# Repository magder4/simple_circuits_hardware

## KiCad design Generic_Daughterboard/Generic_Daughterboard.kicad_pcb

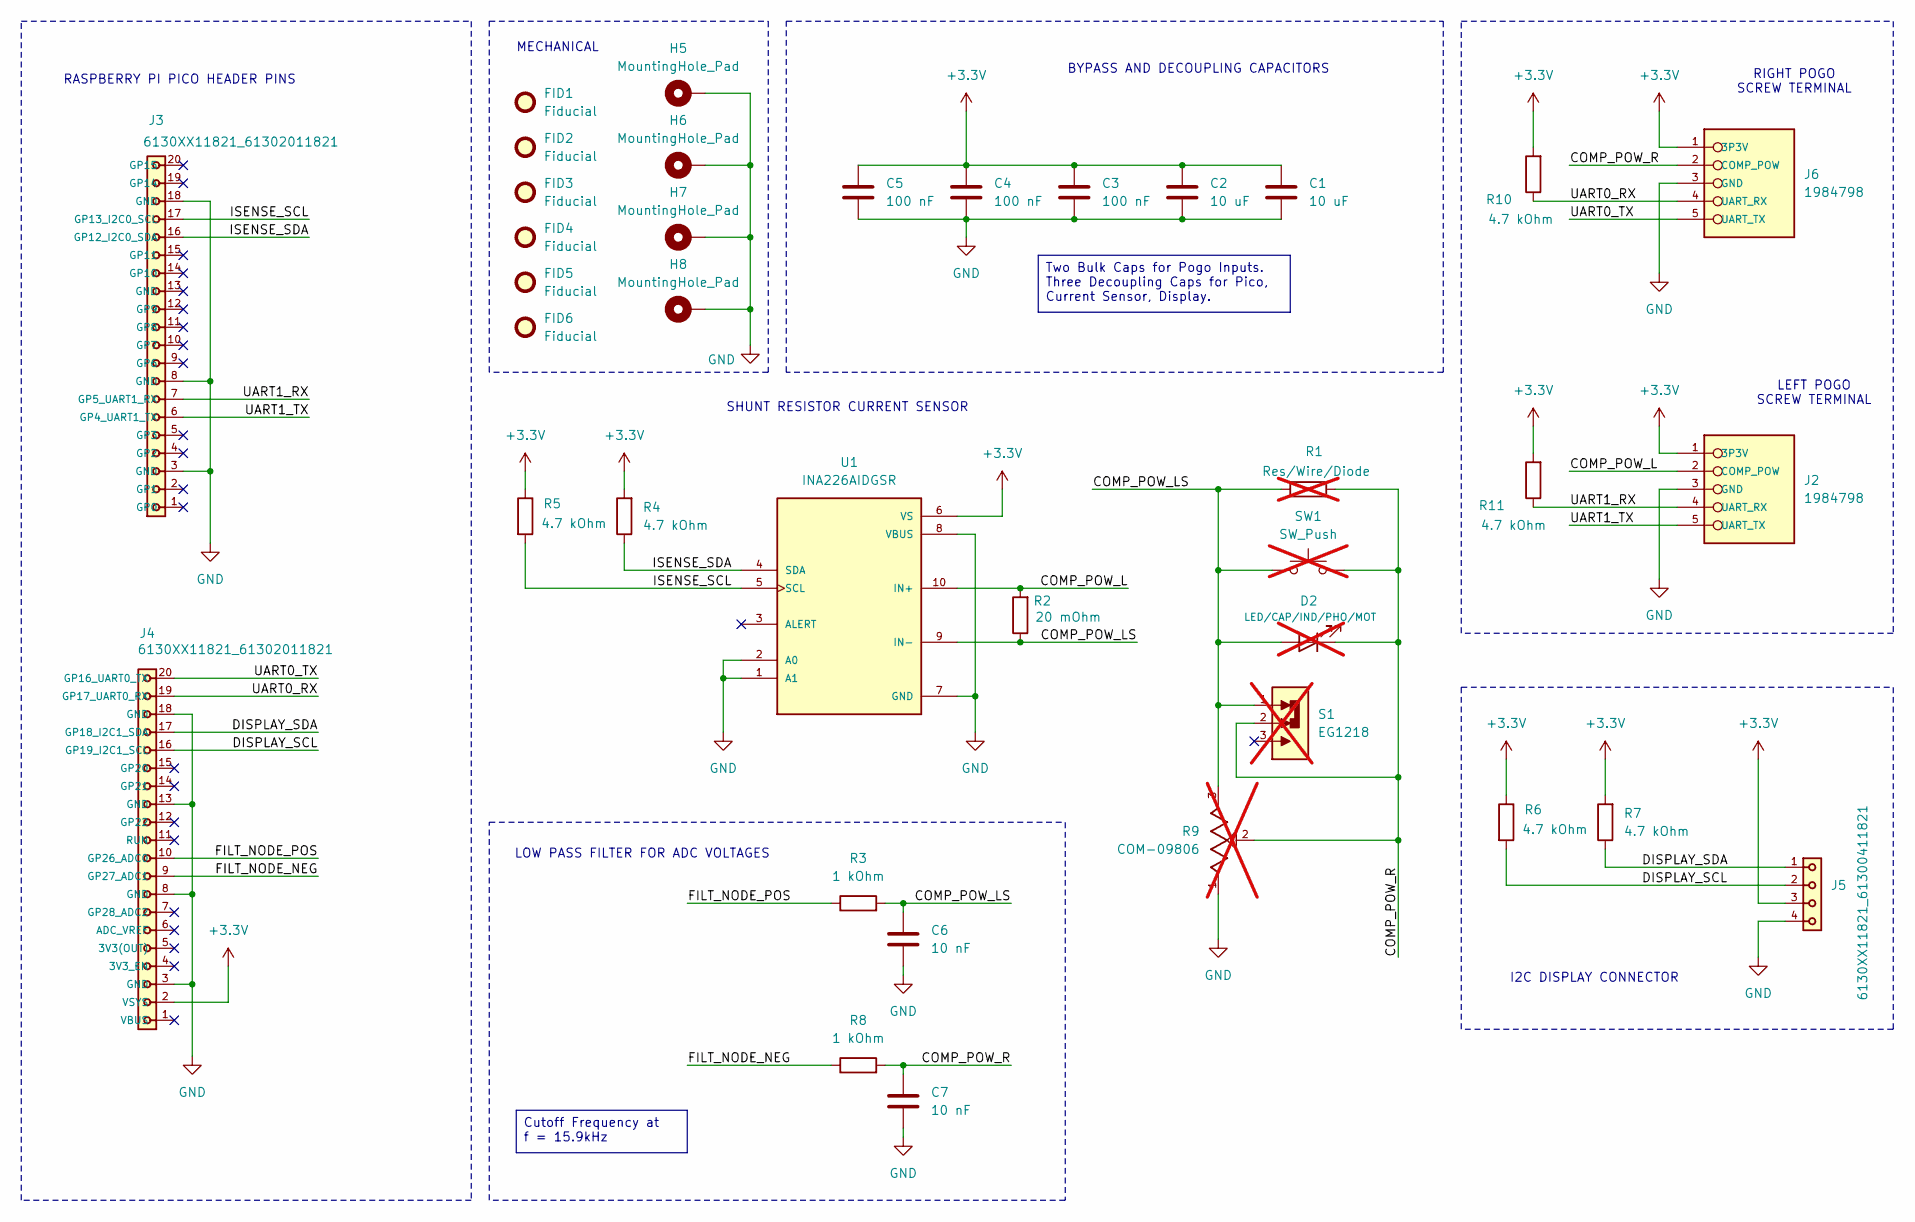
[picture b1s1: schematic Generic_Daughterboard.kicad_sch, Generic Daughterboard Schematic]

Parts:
C1, C2: 10 uF; C_0402_1005Metric
C3, C4, C5: 100 nF; C_0402_1005Metric
C6, C7: 10 nF; C_0402_1005Metric
D2: LED/CAP/IND/PHO/MOT; LED_D5.0mm_Clear; not fitted
FID1, FID2, FID3, FID4, FID5, FID6: Fiducial; Fiducial_0.5mm_Mask1.5mm
H5, H6, H7, H8: MountingHole_Pad; MountingHole_2.2mm_M2_Pad
J2, J6: 1984798; PHOENIX_1984798; MPN 1984798
J3, J4: 6130XX11821_61302011821; 61302011821; DigiKey_Part_Number 732-61302011821-ND
J5: 6130XX11821_61300411821; 61300411821; DigiKey_Part_Number 732-61300411821-ND
R1: Res/Wire/Diode; R_Axial_DIN0207_L6.3mm_D2.5mm_P10.16mm_Horizontal; not fitted
R2: 20 mOhm; R_0805_2012Metric
R3, R8: 1 kOhm; R_0402_1005Metric
R4, R5, R6, R7, R10, R11: 4.7 kOhm; R_0603_1608Metric
R9: COM-09806; TRIM_COM-09806; MPN COM-09806; not fitted
S1: EG1218; SW_EG1218; MPN EG1218; not fitted
SW1: SW_Push; SW_TH_Tactile_Omron_B3F-102x; not fitted
U1: INA226AIDGSR; SOP50P490X110-10N; PARTREV B; DigiKey_Part_Number 296-29034-1-ND

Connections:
+3.3V: C1.1, C2.2, C3.2, C4.2, C5.2, J2.1 (3P3V), J4.2 (VSYS), J5.3, J6.1 (3P3V), R4.2, R5.1, R6.1, R7.2, R10.2, R11.2, U1.6 (VS)
/COMP_POW_L: J2.2 (COMP_POW), R2.2, U1.10 (IN+)
/COMP_POW_LS: C6.2, D2.2 (A), R1.2, R2.1, R3.2, R9.3, S1.1, SW1.1, U1.9 (IN-)
/COMP_POW_R: C7.2, D2.1 (K), J6.2 (COMP_POW), R1.1, R8.2, R9.2, S1.2, SW1.2
/DISPLAY_SCL: J4.16 (GP19_I2C1_SCL), J5.2, R6.2
/DISPLAY_SDA: J4.17 (GP18_I2C1_SDA), J5.1, R7.1
/FILT_NODE_NEG: J4.9 (GP27_ADC1), R8.1
/FILT_NODE_POS: J4.10 (GP26_ADC0), R3.1
/ISENSE_SCL: J3.17 (GP13_I2C0_SCL), R5.2, U1.5 (SCL)
/ISENSE_SDA: J3.16 (GP12_I2C0_SDA), R4.1, U1.4 (SDA)
/UART0_RX: J4.19 (GP17_UART0_RX), J6.4 (UART_RX), R10.1
/UART0_TX: J4.20 (GP16_UART0_TX), J6.5 (UART_TX)
/UART1_RX: J2.4 (UART_RX), J3.7 (GP5_UART1_RX), R11.1
/UART1_TX: J2.5 (UART_TX), J3.6 (GP4_UART1_TX)
GND: C1.2, C2.1, C3.1, C4.1, C5.1, C6.1, C7.1, H5.1 (1_1), H6.1 (1_1), H7.1 (1_1), H8.1 (1_1), J2.3 (GND), J3.3 (GND), J3.8 (GND), J3.18 (GND), J4.3 (GND), J4.8 (GND), J4.13 (GND), J4.18 (GND), J5.4, J6.3 (GND), R9.1, U1.1 (A1), U1.2 (A0), U1.7 (GND), U1.8 (VBUS)

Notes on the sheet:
LEFT POGO SCREW TERMINAL
RASPBERRY PI PICO HEADER PINS
MECHANICAL
BYPASS AND DECOUPLING CAPACITORS
I2C DISPLAY CONNECTOR
RIGHT POGO SCREW TERMINAL
LOW PASS FILTER FOR ADC VOLTAGES
SHUNT RESISTOR CURRENT SENSOR
Cutoff Frequency at f = 15.9kHz
Two Bulk Caps for Pogo Inputs. Three Decoupling Caps for Pico, Current Sensor, Display.

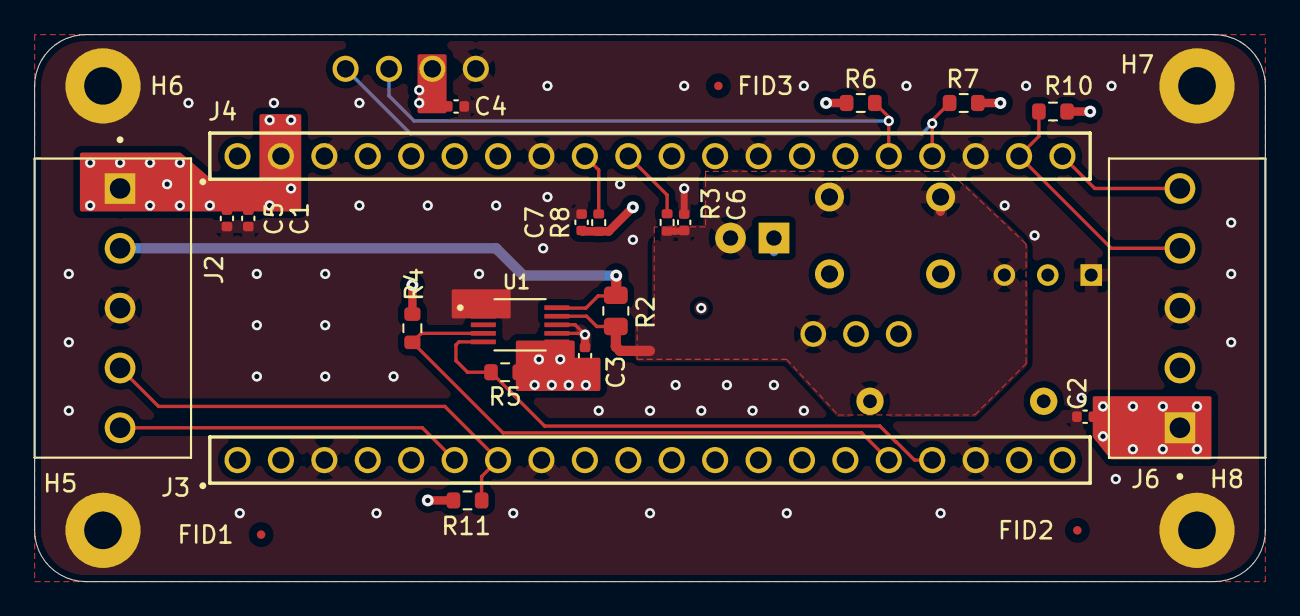
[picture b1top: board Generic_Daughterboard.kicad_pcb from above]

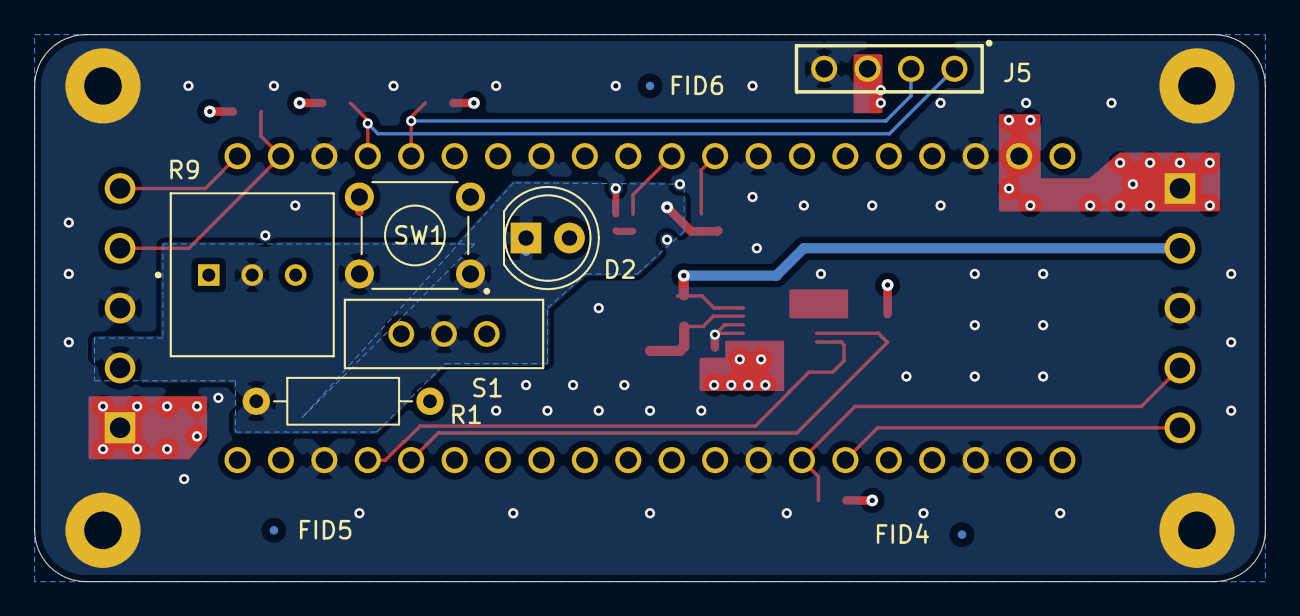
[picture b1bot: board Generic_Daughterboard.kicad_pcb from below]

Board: 4 copper layers, 72.0 x 32.0 mm, 37 parts (9 on the bottom side), 15 nets.
